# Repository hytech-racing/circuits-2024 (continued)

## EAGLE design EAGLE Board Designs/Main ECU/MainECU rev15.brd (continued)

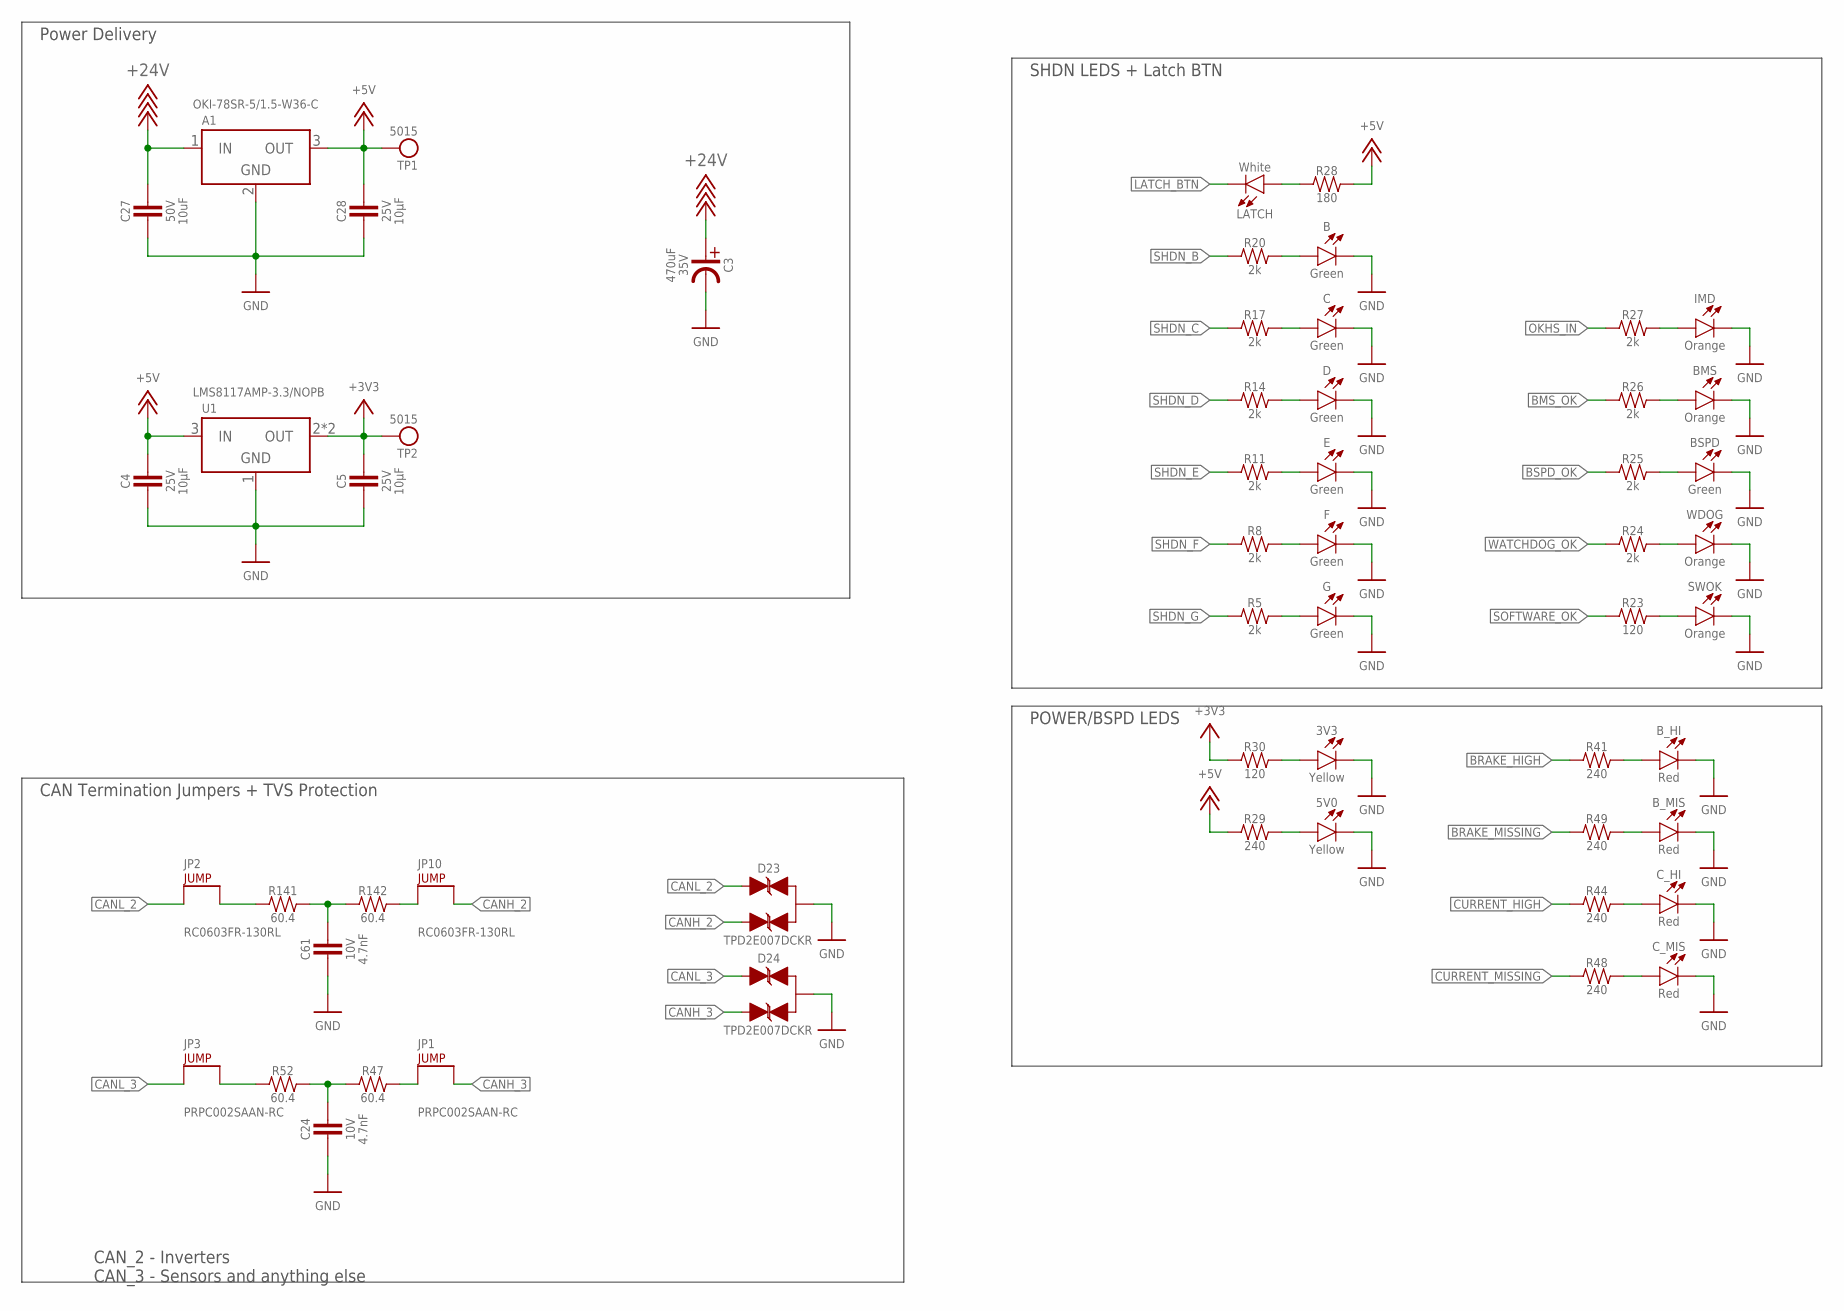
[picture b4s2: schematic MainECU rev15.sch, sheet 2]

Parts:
3V3, 5V0: LED_0603_YELLOW; 0603-LED
A1: VOLTAGE_REGULATOR_MODULE_OKI-78SR_5V; OKI-78SR(VERTICAL)
B: LED_0603_GREEN; 0603-LED
BMS: LED_0603_ORANGE; 0603-LED
BSPD: LED_0603_GREEN; 0603-LED
B_HI: LED_0603_RED; 0603-LED
B_MIS: LED_0603_RED; 0603-LED
C: LED_0603_GREEN; 0603-LED
C3: CAPACITOR_ELECTROLYTIC_EEH_AZS_470UF; EEH-AZS
C4, C5, C28: CAPACITOR_0603_25V_10UF; 0603-CAP
C24, C61: CAPACITOR_0603_10V_4.7NF; 0603-CAP
C27: CAPACITOR_0805_50V_10UF; 0805-CAP
C_HI: LED_0603_RED; 0603-LED
C_MIS: LED_0603_RED; 0603-LED
D: LED_0603_GREEN; 0603-LED
D23, D24: TVS_BIDIRECTIONAL_DUAL; SC-70-3
E: LED_0603_GREEN; 0603-LED
F: LED_0603_GREEN; 0603-LED
G: LED_0603_GREEN; 0603-LED
IMD: LED_0603_ORANGE; 0603-LED
JP1, JP3: JUMPER__1X02; 1X02
JP2, JP10: JUMPER_0603_; 0603-RES
LATCH: LED_0603_WHITE; 0603-LED
R5, R8, R11, R14, R17, R20, R24, R25, R26, R27: RESISTOR_0603_2K; 0603-RES
R23, R30: RESISTOR_0603_120; 0603-RES
R28: RESISTOR_0603_180; 0603-RES
R29, R41, R44, R48, R49: RESISTOR_0603_240; 0603-RES
R47, R52, R141, R142: RESISTOR_0603_60.4; 0603-RES
SWOK: LED_0603_ORANGE; 0603-LED
TP1, TP2: TEST_POINT; 5015
U1: VOLTAGE_REGULATOR_SOT-223_3.3V; SOT-223
WDOG: LED_0603_ORANGE; 0603-LED

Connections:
+3V3: C5.1, R30.1, TP2.1, U1.2 (OUT), U1.4 (OUT); also elsewhere on the board
+5V: A1.3 (OUT), C4.1, C28.1, R28.2, R29.1, TP1.1, U1.3 (IN); also elsewhere on the board
+24V: A1.1 (IN), C3.PLUS, C27.1; also elsewhere on the board
BMS_OK: R26.1; also elsewhere on the board
BRAKE_HIGH: R41.1; also elsewhere on the board
BRAKE_MISSING: R49.1; also elsewhere on the board
BSPD_OK: R25.1; also elsewhere on the board
CANH_2: D23.2 (C2), JP10.2; also elsewhere on the board
CANH_3: D24.2 (C2), JP1.2; also elsewhere on the board
CANL_2: D23.1 (C1), JP2.1; also elsewhere on the board
CANL_3: D24.1 (C1), JP3.1; also elsewhere on the board
CURRENT_HIGH: R44.1; also elsewhere on the board
CURRENT_MISSING: R48.1; also elsewhere on the board
GND: 3V3.1 (C), 5V0.1 (C), A1.2 (GND), B.1 (C), BMS.1 (C), BSPD.1 (C), B_HI.1 (C), B_MIS.1 (C), C.1 (C), C3.MINUS, C4.2, C5.2, C24.2, C27.2, C28.2, C61.2, C_HI.1 (C), C_MIS.1 (C), D.1 (C), D23.3 (A), D24.3 (A), E.1 (C), F.1 (C), G.1 (C), IMD.1 (C), SWOK.1 (C), U1.1 (GND), WDOG.1 (C); also elsewhere on the board
LATCH_BTN: LATCH.1 (C); also elsewhere on the board
unnamed: JP10.1, R142.2
unnamed: JP1.1, R47.2
unnamed: C61.1, R141.2, R142.1
unnamed: C24.1, R47.1, R52.2
unnamed: JP3.2, R52.1
unnamed: G.2 (A), R5.2
unnamed: LATCH.2 (A), R28.1
unnamed: B.2 (A), R20.2
unnamed: C.2 (A), R17.2
unnamed: D.2 (A), R14.2
unnamed: E.2 (A), R11.2
unnamed: F.2 (A), R8.2
unnamed: B_MIS.2 (A), R49.2
unnamed: C_HI.2 (A), R44.2
unnamed: C_MIS.2 (A), R48.2
unnamed: JP2.2, R141.1
unnamed: IMD.2 (A), R27.2
unnamed: BMS.2 (A), R26.2
unnamed: BSPD.2 (A), R25.2
unnamed: R24.2, WDOG.2 (A)
unnamed: 3V3.2 (A), R30.2
unnamed: R23.2, SWOK.2 (A)
unnamed: 5V0.2 (A), R29.2
unnamed: B_HI.2 (A), R41.2
OKHS_IN: R27.1; also elsewhere on the board
SHDN_B: R20.1; also elsewhere on the board
SHDN_C: R17.1; also elsewhere on the board
SHDN_D: R14.1; also elsewhere on the board
SHDN_E: R11.1; also elsewhere on the board
SHDN_F: R8.1; also elsewhere on the board
SHDN_G: R5.1; also elsewhere on the board
SOFTWARE_OK: R23.1; also elsewhere on the board
WATCHDOG_OK: R24.1; also elsewhere on the board

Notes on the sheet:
CAN_2 - Inverters CAN_3 - Sensors and anything else
Power Delivery
SHDN LEDS + Latch BTN
POWER/BSPD LEDS
CAN Termination Jumpers + TVS Protection

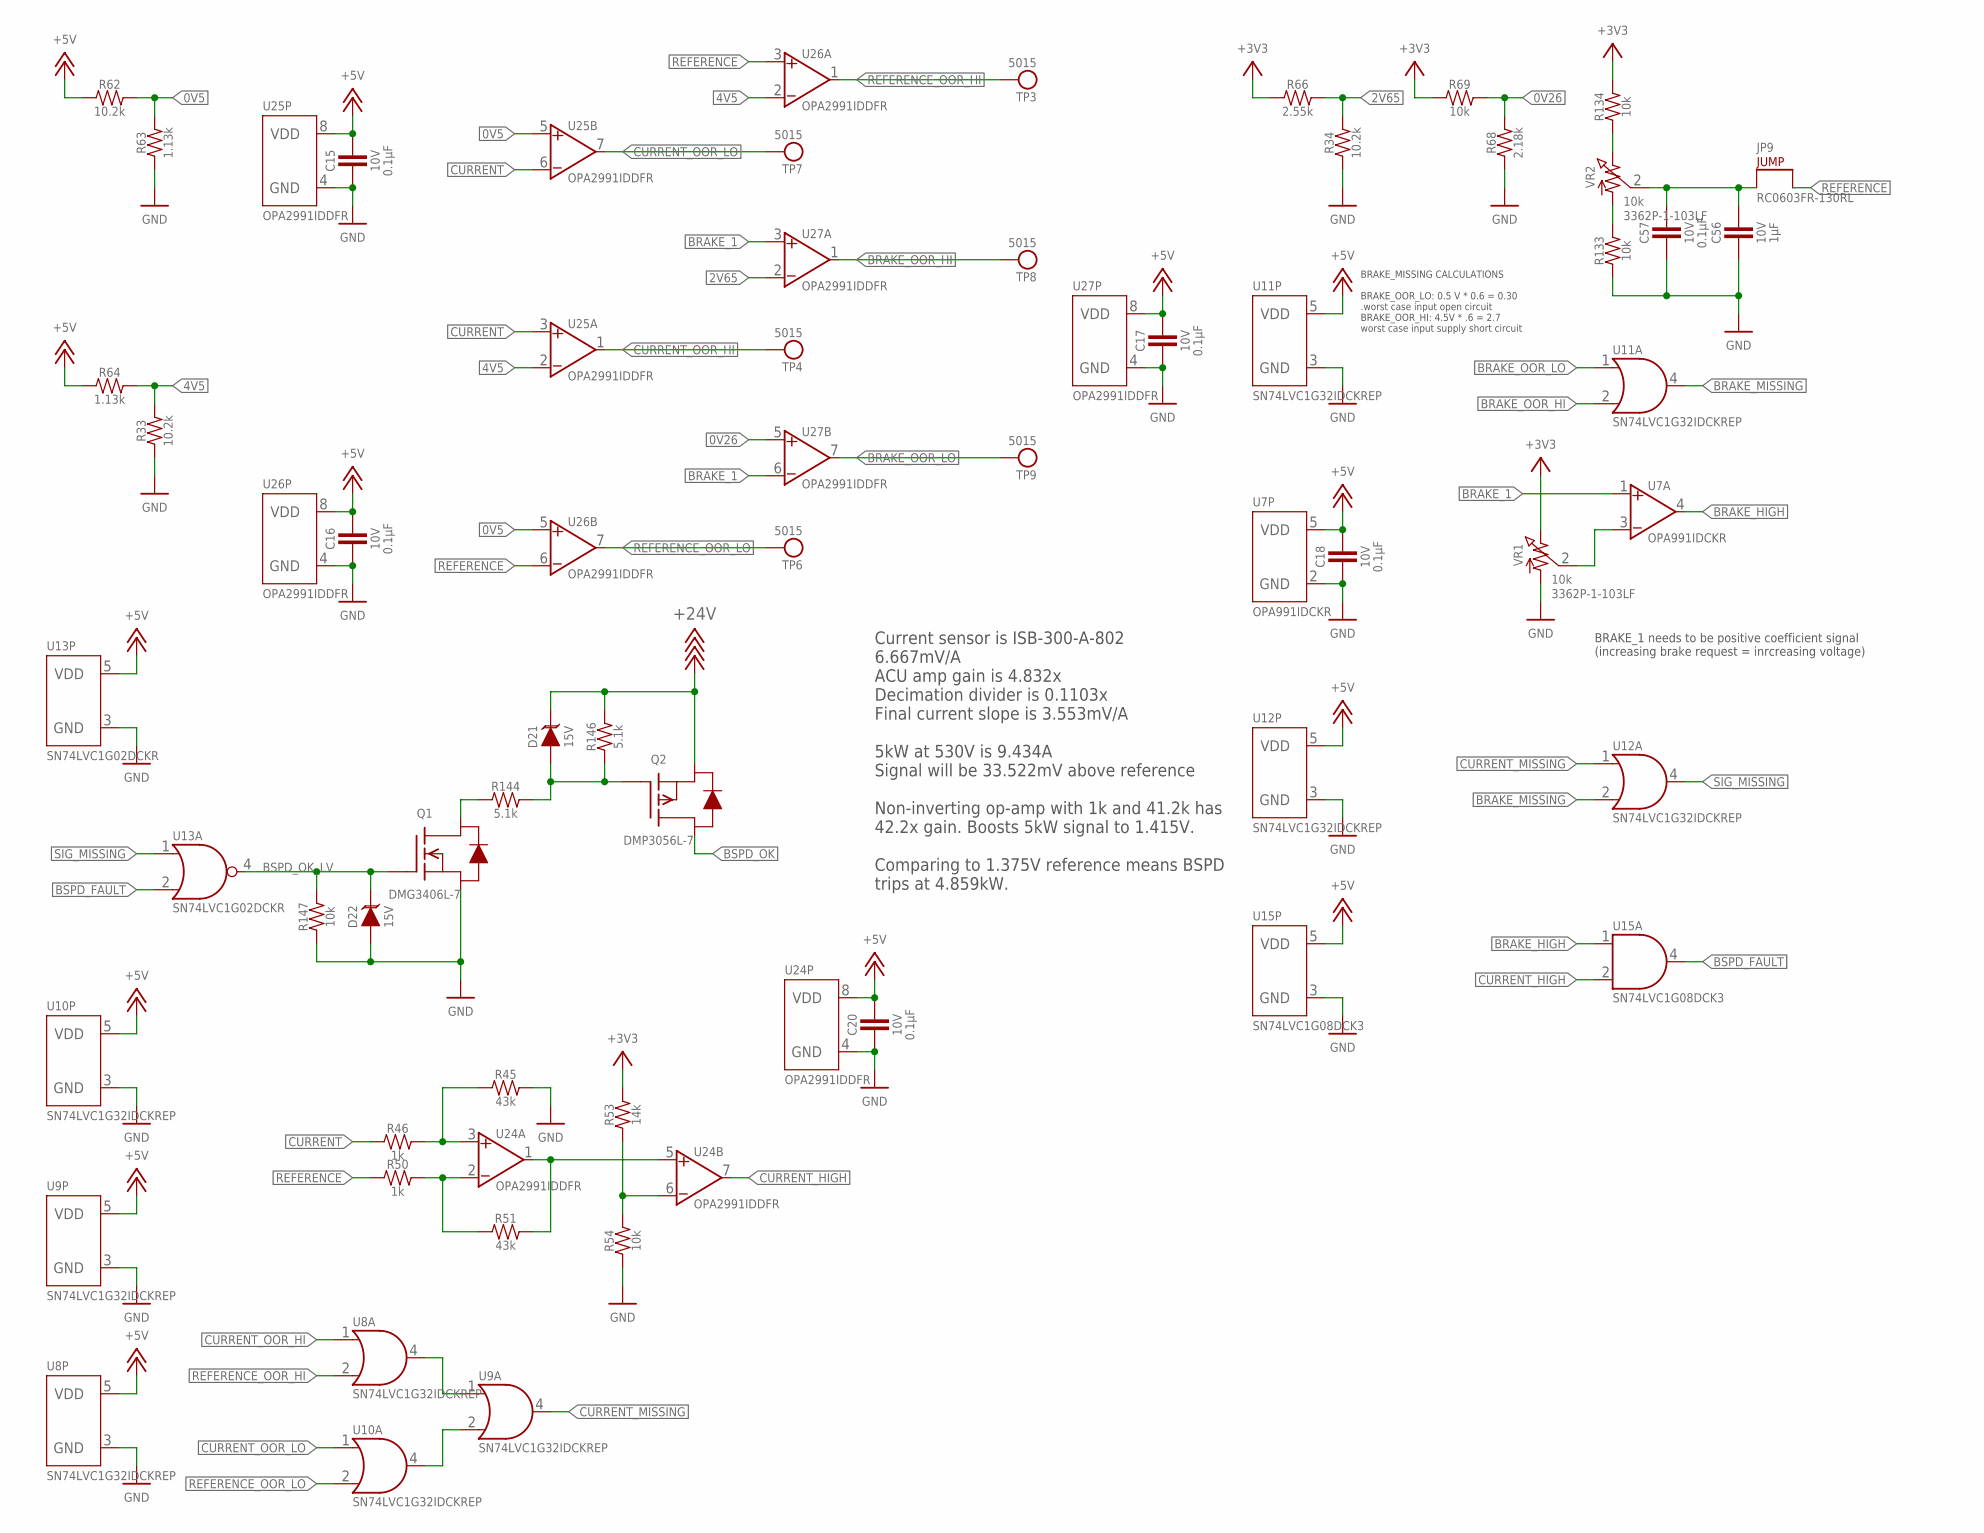
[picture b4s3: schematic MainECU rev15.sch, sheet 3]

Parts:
C15, C16, C17, C18, C20, C57: CAPACITOR_0603_10V_0.1UF; 0603-CAP
C56: CAPACITOR_0603_10V_1UF; 0603-CAP
D21, D22: TVS__15V; SOT-23
JP9: DNP; 0603-RES
Q1: TRANSISTOR_N_MOS__DMG3406L-7; SOT-23
Q2: TRANSISTOR_P_MOS_SOT-23_DMP3056L-7; SOT-23
R33, R34, R62: RESISTOR_0603_10.2K; 0603-RES
R45, R51: RESISTOR_0603_43K; 0603-RES
R46, R50: RESISTOR_0603_1K; 0603-RES
R53: RESISTOR_0603_14K; 0603-RES
R54, R69, R133, R134, R147: RESISTOR_0603_10K; 0603-RES
R63, R64: RESISTOR_0603_1.13K; 0603-RES
R66: RESISTOR_0603_2.55K; 0603-RES
R68: RESISTOR_0603_2.18K; 0603-RES
R144, R146: RESISTOR_0603_5.1K; 0603-RES
TP3, TP4, TP6, TP7, TP8, TP9: TEST_POINT; 5015
U7: OPAMP_1_CHANNEL_OPA991; SC-70-5
U8, U9, U10, U11, U12: LOGICGATE_OR; SC-70-5
U13: LOGICGATE_NOR; SC-70-5
U15: LOGICGATE_AND_DCK3; SC-70-5
U24, U25, U26, U27: OPAMP_2_CHANNEL_OPA_2991; SOT-23-8
VR1, VR2: RESISTOR_TRIMPOT_10K_3362P; 3362P

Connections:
0V5: R62.2, R63.2, U25.5 (VIN+), U26.5 (VIN+)
0V26: R68.2, R69.2, U27.5 (VIN+)
2V65: R34.2, R66.2, U27.2 (VIN-)
4V5: R33.2, R64.2, U25.2 (VIN-), U26.2 (VIN-)
+3V3: R53.2, R66.1, R69.1, R134.2, VR1.3 (2); also elsewhere on the board
+5V: C15.1, C16.1, C17.1, C18.1, C20.1, R62.1, R64.1, U7.5 (VDD), U8.5 (VDD), U9.5 (VDD), U10.5 (VDD), U11.5 (VDD), U12.5 (VDD), U13.5 (VDD), U15.5 (VDD), U24.8 (VDD), U25.8 (VDD), U26.8 (VDD), U27.8 (VDD); also elsewhere on the board
+24V: D21.3 (C), Q2.2 (S), R146.2; also elsewhere on the board
BRAKE_1: U7.1 (VIN+), U27.3 (VIN+), U27.6 (VIN-); also elsewhere on the board
BRAKE_HIGH: U7.4 (VOUT), U15.1 (IN1); also elsewhere on the board
BRAKE_MISSING: U11.4 (OUT), U12.2 (IN2); also elsewhere on the board
BRAKE_OOR_HI: TP8.1, U11.2 (IN2), U27.1 (VOUT)
BRAKE_OOR_LO: TP9.1, U11.1 (IN1), U27.7 (VOUT)
BSPD_FAULT: U13.2 (IN2), U15.4 (OUT)
BSPD_OK: Q2.3 (D); also elsewhere on the board
BSPD_OK_LV: D22.3 (C), Q1.1 (G), R147.2, U13.4 (OUT)
CURRENT: R46.1, U25.3 (VIN+), U25.6 (VIN-); also elsewhere on the board
CURRENT_HIGH: U15.2 (IN2), U24.7 (VOUT); also elsewhere on the board
CURRENT_MISSING: U9.4 (OUT), U12.1 (IN1); also elsewhere on the board
CURRENT_OOR_HI: TP4.1, U8.1 (IN1), U25.1 (VOUT)
CURRENT_OOR_LO: TP7.1, U10.1 (IN1), U25.7 (VOUT)
GND: C15.2, C16.2, C17.2, C18.2, C20.2, C56.2, C57.2, D22.1 (A), Q1.2 (S), R33.1, R34.1, R45.2, R54.1, R63.1, R68.1, R133.1, R147.1, U7.2 (GND), U8.3 (GND), U9.3 (GND), U10.3 (GND), U11.3 (GND), U12.3 (GND), U13.3 (GND), U15.3 (GND), U24.4 (GND), U25.4 (GND), U26.4 (GND), U27.4 (GND), VR1.1; also elsewhere on the board
unnamed: R45.1, R46.2, U24.3 (VIN+)
unnamed: R134.1, VR2.3 (2)
unnamed: C56.1, C57.1, JP9.1, VR2.2 (3)
unnamed: R133.2, VR2.1
unnamed: R53.1, R54.2, U24.6 (VIN-)
unnamed: R50.2, R51.1, U24.2 (VIN-)
unnamed: R51.2, U24.1 (VOUT), U24.5 (VIN+)
unnamed: U7.3 (VIN-), VR1.2 (3)
unnamed: D21.1 (A), Q2.1 (G), R144.2, R146.1
unnamed: Q1.3 (D), R144.1
OOR_HI: U8.4 (OUT), U9.1 (IN1)
OOR_LO: U9.2 (IN2), U10.4 (OUT)
REFERENCE: JP9.2, R50.1, U26.3 (VIN+), U26.6 (VIN-); also elsewhere on the board
REFERENCE_OOR_HI: TP3.1, U8.2 (IN2), U26.1 (VOUT)
REFERENCE_OOR_LO: TP6.1, U10.2 (IN2), U26.7 (VOUT)
SIG_MISSING: U12.4 (OUT), U13.1 (IN1)

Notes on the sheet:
Current sensor is ISB-300-A-802 6.667mV/A ACU amp gain is 4.832x Decimation divider is 0.1103x Final current slope is 3.553mV/A 5kW at 530V is 9.434A Signal will be 33.522mV above reference Non-inverting op-amp with 1k and 41.2k has 42.2x gain. Boosts 5kW signal to 1.415V. Comparing to 1.375V refer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
BRAKE_1 needs to be positive coefficient signal (increasing brake request = inrcreasing voltage)
BRAKE_MISSING CALCULATIONS BRAKE_OOR_LO: 0.5 V * 0.6 = 0.30 .worst case input open circuit BRAKE_OOR_HI: 4.5V * .6 = 2.7 worst case input supply short circuit

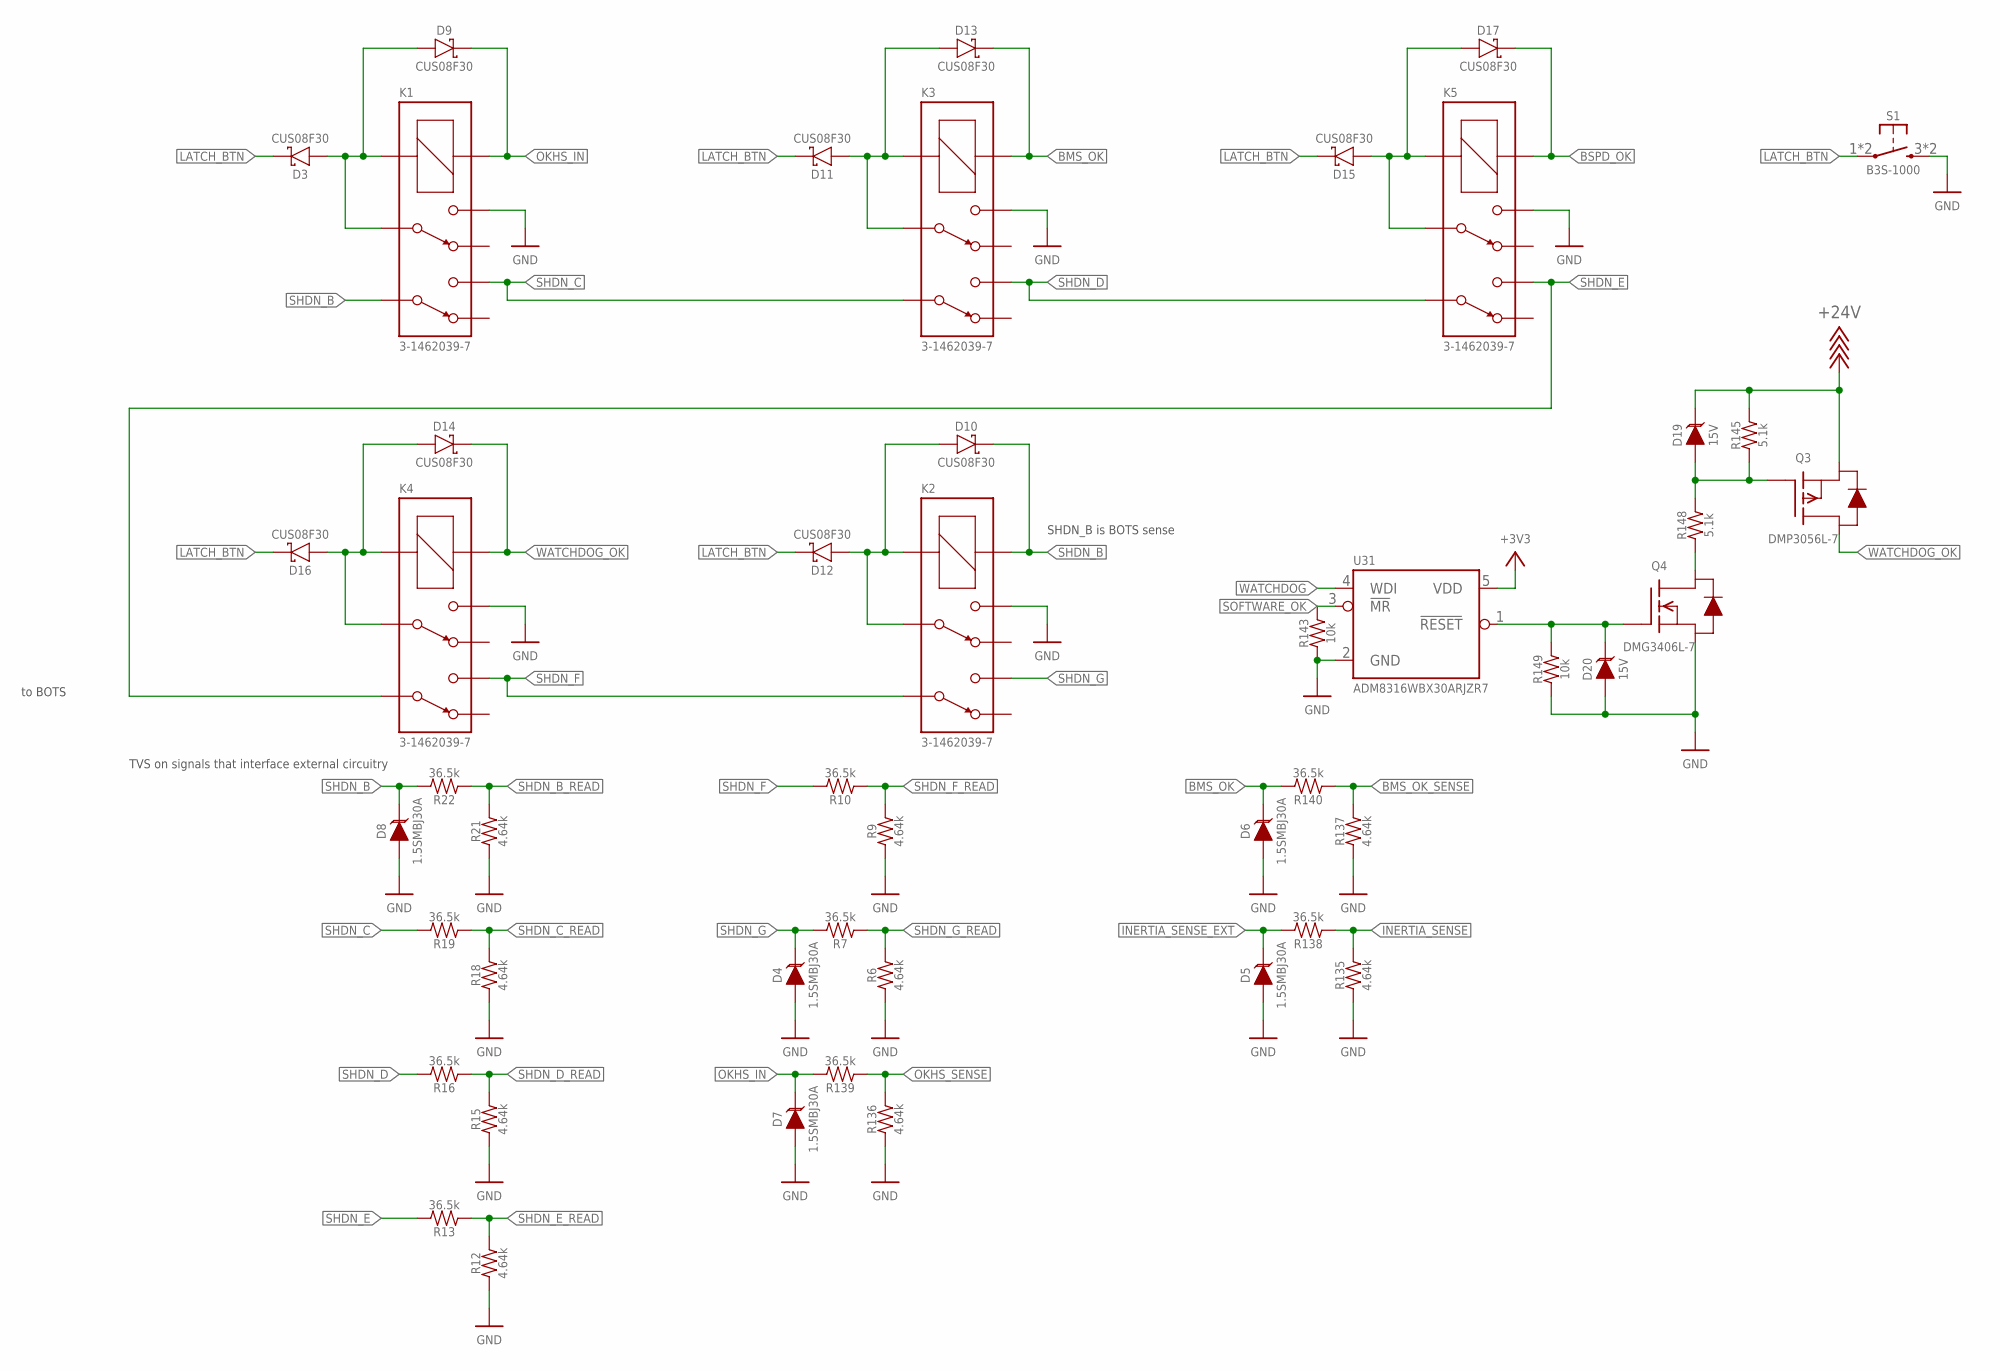
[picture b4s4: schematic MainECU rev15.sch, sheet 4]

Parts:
D3, D9, D10, D11, D12, D13, D14, D15, D16, D17: SCHOTTKY_SOD323_30V; SOD-323
D4, D5, D6, D7, D8: TVS_DO-214AA_30V; 1.5SMBJ
D19, D20: TVS__15V; SOT-23
K1, K2, K3, K4, K5: RELAY_DPDT_07DSMT; IM*G
Q3: TRANSISTOR_P_MOS_SOT-23_DMP3056L-7; SOT-23
Q4: TRANSISTOR_N_MOS__DMG3406L-7; SOT-23
R6, R9, R12, R15, R18, R21, R135, R136, R137: RESISTOR_0603_4.64K; 0603-RES
R7, R10, R13, R16, R19, R22, R138, R139, R140: RESISTOR_0603_36.5K; 0603-RES
R143, R149: RESISTOR_0603_10K; 0603-RES
R145, R148: RESISTOR_0603_5.1K; 0603-RES
S1: BUTTON; B3S-100X
U31: ADM8316WBX30; SOT-23-5

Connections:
+3V3: U31.5 (VDD); also elsewhere on the board
+24V: D19.3 (C), Q3.2 (S), R145.2; also elsewhere on the board
BMS_OK: D6.2 (C), D13.C, K3.1 (COIL+), R140.2; also elsewhere on the board
BMS_OK_SENSE: R137.2, R140.1; also elsewhere on the board
BSPD_OK: D17.C, K5.1 (COIL+); also elsewhere on the board
GND: D4.1 (A), D5.1 (A), D6.1 (A), D7.1 (A), D8.1 (A), D20.1 (A), K1.4, K2.4, K3.4, K4.4, K5.4, Q4.2 (S), R6.1, R9.1, R12.1, R15.1, R18.1, R21.1, R135.1, R136.1, R137.1, R143.1, R149.1, S1.3 (S), S1.4 (S), U31.2 (GND); also elsewhere on the board
INERTIA_SENSE: R135.2, R138.1; also elsewhere on the board
INERTIA_SENSE_EXT: D5.2 (C), R138.2; also elsewhere on the board
LATCH_BTN: D3.C, D11.C, D12.C, D15.C, D16.C, S1.1, S1.2; also elsewhere on the board
unnamed: D19.1 (A), Q3.1 (G), R145.1, R148.2
unnamed: Q4.3 (D), R148.1
unnamed: D3.A, D9.A, K1.3, K1.8 (COIL-)
unnamed: D15.A, D17.A, K5.3, K5.8 (COIL-)
unnamed: D11.A, D13.A, K3.3, K3.8 (COIL-)
unnamed: D10.A, D12.A, K2.3, K2.8 (COIL-)
unnamed: D14.A, D16.A, K4.3, K4.8 (COIL-)
OKHS_IN: D7.2 (C), D9.C, K1.1 (COIL+), R139.2; also elsewhere on the board
OKHS_SENSE: R136.2, R139.1; also elsewhere on the board
SHDN_B: D8.2 (C), D10.C, K1.6, K2.1 (COIL+), R22.2; also elsewhere on the board
SHDN_B_READ: R21.2, R22.1; also elsewhere on the board
SHDN_C: K1.5, K3.6, R19.2; also elsewhere on the board
SHDN_C_READ: R18.2, R19.1; also elsewhere on the board
SHDN_D: K3.5, K5.6, R16.2; also elsewhere on the board
SHDN_D_READ: R15.2, R16.1; also elsewhere on the board
SHDN_E: K4.6, K5.5, R13.2; also elsewhere on the board
SHDN_E_READ: R12.2, R13.1; also elsewhere on the board
SHDN_F: K2.6, K4.5, R10.2; also elsewhere on the board
SHDN_F_READ: R9.2, R10.1; also elsewhere on the board
SHDN_G: D4.2 (C), K2.5, R7.2; also elsewhere on the board
SHDN_G_READ: R6.2, R7.1; also elsewhere on the board
SOFTWARE_OK: R143.2, U31.3 (!MR!); also elsewhere on the board
WATCHDOG: U31.4 (WDI); also elsewhere on the board
WATCHDOG_OK: D14.C, K4.1 (COIL+), Q3.3 (D); also elsewhere on the board
WATCHDOG_OK_LV: D20.3 (C), Q4.1 (G), R149.2, U31.1 (!RESET!)

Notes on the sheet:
to BOTS
SHDN_B is BOTS sense
TVS on signals that interface external circuitry

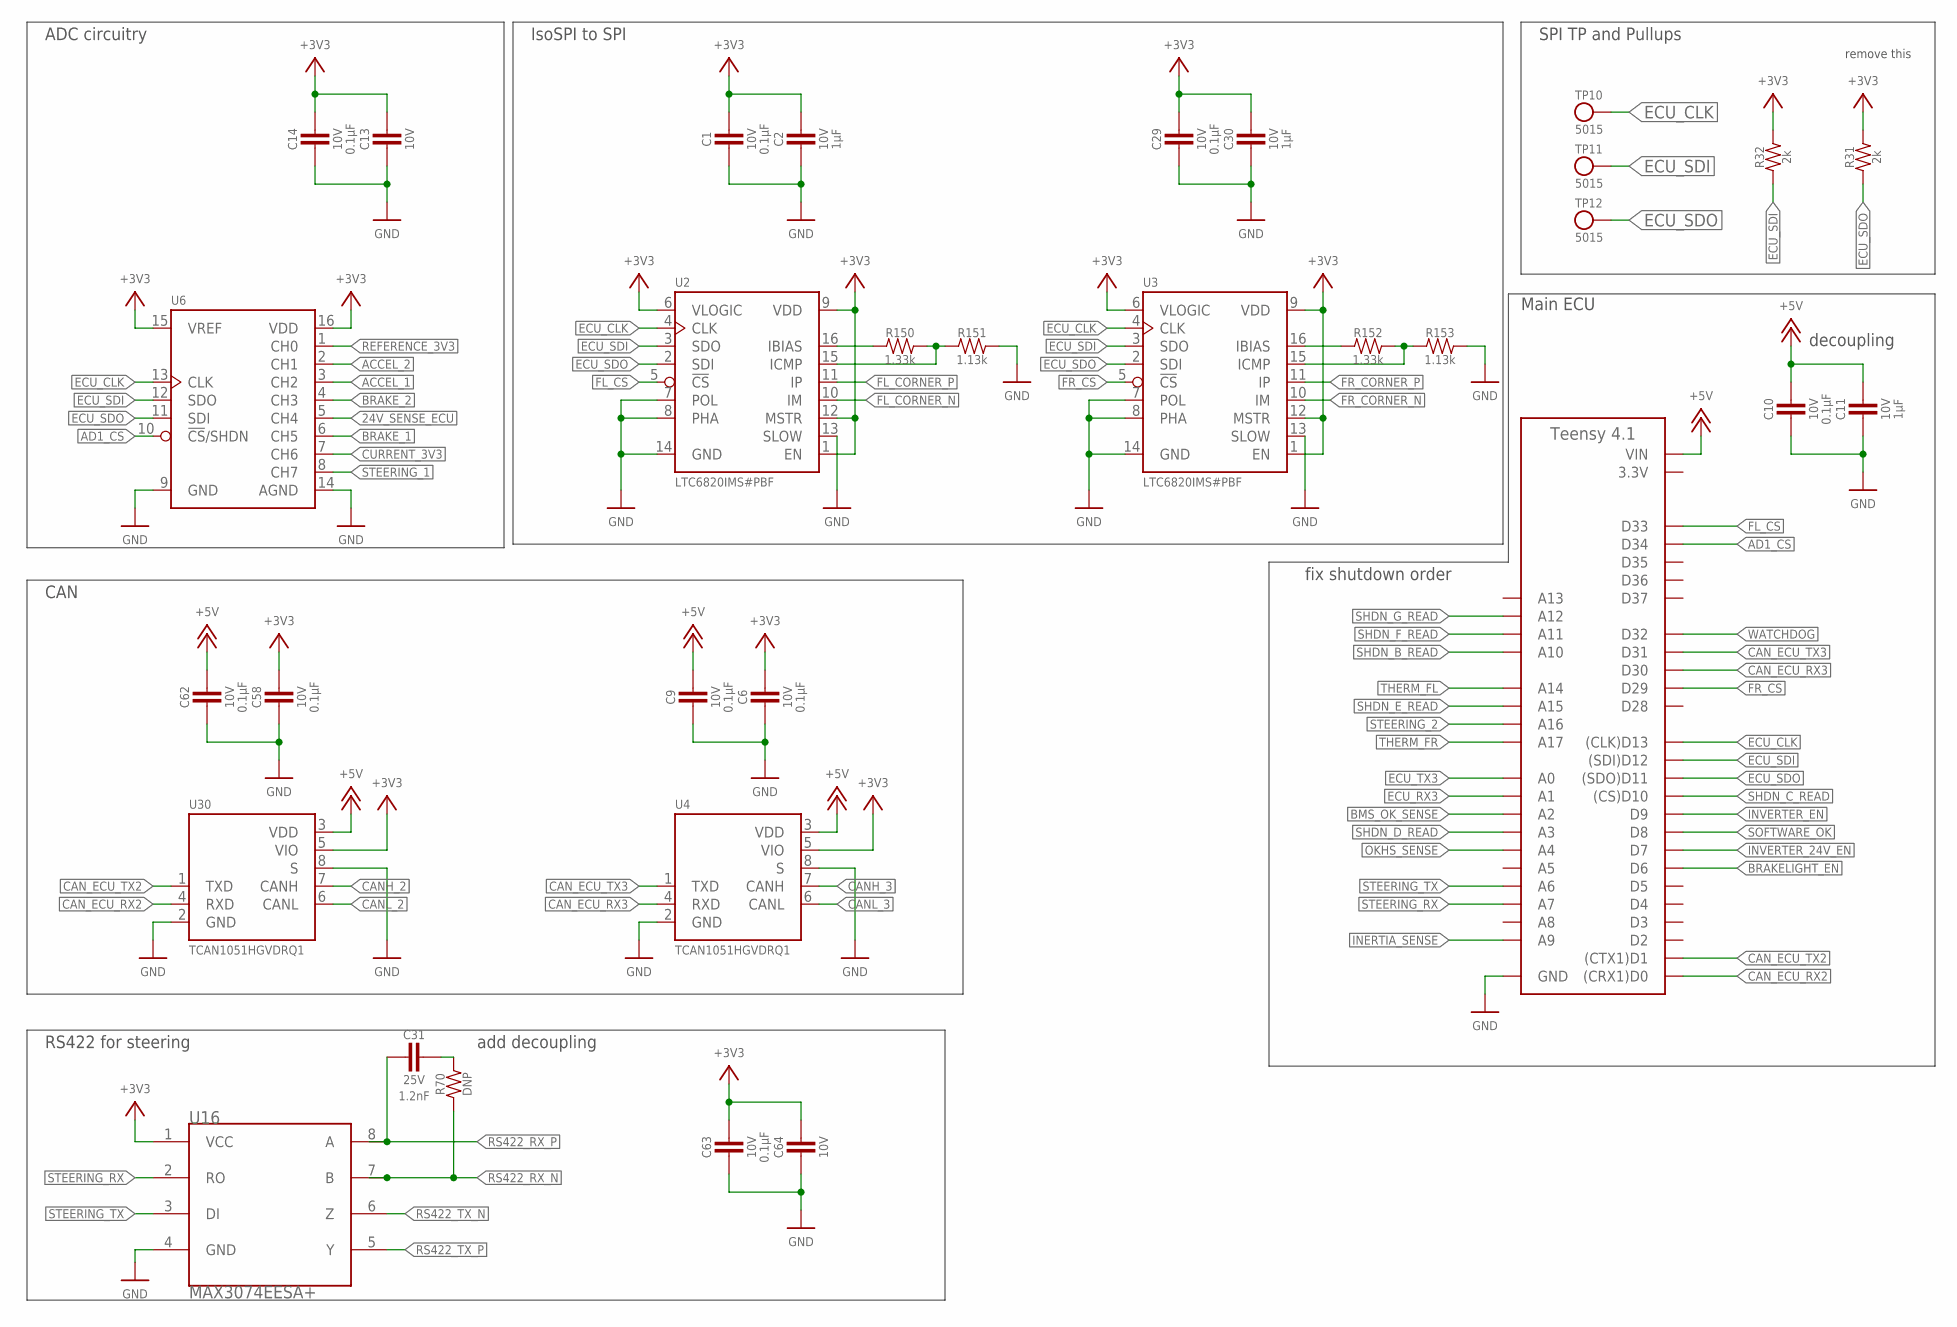
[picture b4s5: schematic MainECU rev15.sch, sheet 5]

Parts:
A2: TEENSY_4.1_SMT; TEENSY_LONG_SSM
C1, C6, C9, C10, C14, C29, C58, C62, C63: CAPACITOR_0603_10V_0.1UF; 0603-CAP
C2, C11, C13, C30, C64: CAPACITOR_0603_10V_1UF; 0603-CAP
C31: CAPACITOR_0603_25V_1.2NF; 0603-CAP
R31, R32: RESISTOR_0603_2K; 0603-RES
R70: RESISTOR_0603_DNP; 0603-RES
R150, R152: RESISTOR_0603_1.33K; 0603-RES
R151, R153: RESISTOR_0603_1.13K; 0603-RES
TP10, TP11, TP12: TEST_POINT; 5015
U2, U3: LTC6820; MSOP-16
U4, U30: TCAN1051HQV-Q1; SOIC-08(NARROW,0.15")
U6: MCP3208; SOIC-16
U16: MAX3074EESA+; SOIC-08(NARROW,0.15")

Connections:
3.3V: A2.3.3V, A2.3.3V@1 (3.3V); also elsewhere on the board
24V_SENSE_ECU: U6.5 (CH4); also elsewhere on the board
!AD1_CS: A2.D34, U6.10 (!CS!/SHDN)
!FL_CS: A2.D33, U2.5 (!CS)
!FR_CS: A2.D29, U3.5 (!CS)
+3V3: C1.1, C2.1, C6.1, C13.1, C14.1, C29.1, C30.1, C58.1, C63.1, C64.1, R31.2, R32.2, U2.1 (EN), U2.6 (VLOGIC), U2.9 (VDD), U2.12 (MSTR), U3.1 (EN), U3.6 (VLOGIC), U3.9 (VDD), U3.12 (MSTR), U4.5 (VIO), U6.15 (VREF), U6.16 (VDD), U16.1 (VCC), U30.5 (VIO); also elsewhere on the board
+5V: A2.VIN, C9.1, C10.1, C11.1, C62.1, U4.3 (VDD), U30.3 (VDD); also elsewhere on the board
ACCEL_1: U6.3 (CH2); also elsewhere on the board
ACCEL_2: U6.2 (CH1); also elsewhere on the board
BMS_OK_SENSE: A2.D16 (A2); also elsewhere on the board
BRAKELIGHT_EN: A2.D6; also elsewhere on the board
BRAKE_1: U6.6 (CH5); also elsewhere on the board
BRAKE_2: U6.4 (CH3); also elsewhere on the board
CANH_2: U30.7 (CANH); also elsewhere on the board
CANH_3: U4.7 (CANH); also elsewhere on the board
CANL_2: U30.6 (CANL); also elsewhere on the board
CANL_3: U4.6 (CANL); also elsewhere on the board
CAN_ECU_RX2: A2.D0 ((CRX1)D0), U30.4 (RXD)
CAN_ECU_RX3: A2.D30, U4.4 (RXD)
CAN_ECU_TX2: A2.D1 ((CTX1)D1), U30.1 (TXD)
CAN_ECU_TX3: A2.D31, U4.1 (TXD)
CURRENT_3V3: U6.7 (CH6); also elsewhere on the board
ECU_CLK: A2.D13 ((CLK)D13), TP10.1, U2.4 (CLK), U3.4 (CLK), U6.13 (CLK)
ECU_RX3: A2.D15 (A1); also elsewhere on the board
ECU_SDI: A2.D12 ((SDI)D12), R32.1, TP11.1, U2.3 (SDO), U3.3 (SDO), U6.12 (SDO)
ECU_SDO: A2.D11 ((SDO)D11), R31.1, TP12.1, U2.2 (SDI), U3.2 (SDI), U6.11 (SDI)
ECU_TX3: A2.D14 (A0); also elsewhere on the board
FL_CORNER_N: U2.10 (IM); also elsewhere on the board
FL_CORNER_P: U2.11 (IP); also elsewhere on the board
FR_CORNER_N: U3.10 (IM); also elsewhere on the board
FR_CORNER_P: U3.11 (IP); also elsewhere on the board
GND: A2.AGND/GND (GND), A2.GND, A2.GND@1 (GND), C1.2, C2.2, C6.2, C9.2, C10.2, C11.2, C13.2, C14.2, C29.2, C30.2, C58.2, C62.2, C63.2, C64.2, R151.2, R153.2, U2.7 (POL), U2.8 (PHA), U2.13 (SLOW), U2.14 (GND), U3.7 (POL), U3.8 (PHA), U3.13 (SLOW), U3.14 (GND), U4.2 (GND), U4.8 (S), U6.9 (GND), U6.14 (AGND), U16.4 (GND), U30.2 (GND), U30.8 (S); also elsewhere on the board
INERTIA_SENSE: A2.D23 (A9); also elsewhere on the board
INVERTER_24V_EN: A2.D7; also elsewhere on the board
INVERTER_EN: A2.D9; also elsewhere on the board
unnamed: C31.1, R70.2
unnamed: R150.1, U2.16 (IBIAS)
unnamed: R150.2, R151.1, U2.15 (ICMP)
unnamed: R152.1, U3.16 (IBIAS)
unnamed: R152.2, R153.1, U3.15 (ICMP)
OKHS_SENSE: A2.D18 (A4); also elsewhere on the board
REFERENCE_3V3: U6.1 (CH0); also elsewhere on the board
RS422_RX_N: R70.1, U16.7 (B); also elsewhere on the board
RS422_RX_P: C31.2, U16.8 (A); also elsewhere on the board
RS422_TX_N: U16.6 (Z); also elsewhere on the board
RS422_TX_P: U16.5 (Y); also elsewhere on the board
SHDN_B_READ: A2.D24 (A10); also elsewhere on the board
SHDN_C_READ: A2.D10 ((CS)D10); also elsewhere on the board
SHDN_D_READ: A2.D17 (A3); also elsewhere on the board
SHDN_E_READ: A2.D39 (A15); also elsewhere on the board
SHDN_F_READ: A2.D25 (A11); also elsewhere on the board
SHDN_G_READ: A2.D26 (A12); also elsewhere on the board
SOFTWARE_OK: A2.D8; also elsewhere on the board
STEERING_1: U6.8 (CH7); also elsewhere on the board
STEERING_2: A2.D40 (A16); also elsewhere on the board
STEERING_RX: A2.D21 (A7), U16.2 (RO)
STEERING_TX: A2.D20 (A6), U16.3 (DI)
THERM_FL: A2.D38 (A14); also elsewhere on the board
THERM_FR: A2.D41 (A17); also elsewhere on the board
WATCHDOG: A2.D32; also elsewhere on the board

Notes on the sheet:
decoupling
Main ECU
ADC circuitry
IsoSPI to SPI
SPI TP and Pullups
CAN
RS422 for steering
remove this
add decoupling
fix shutdown order
